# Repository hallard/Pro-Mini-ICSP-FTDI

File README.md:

Arduino Pro Mini ICSP and FTDI Programming Board
================================================

This shield is used to flash my Arduino Pro Mini with [OptiBoot](https://github.com/Optiboot/optiboot) bootloader and to upload sketch to it. Optiboot is less Flash consuming than classic one.

Also, for 3V3 at 8MHz devices, upload at 57600 is slow, so I'm using 250KBPS upload. You can see [here](https://hallard.me/ulpnode-bootloader-1/) why and how to. 
So, I can upload faster and more than that, Optiboot is using 0.5K of flash instead of 2K, it's a double win configuration, especially with huge sketch like LoraWan device with LMIC stack for my [Mini LORA Board](https://www.thethingsnetwork.org/forum/t/8059/).

**Features**   

- ICSP 6 pins connector
- FTDI 6 pins connector
- Power LED
- Reset button

**Got V1.0 Boards from [PCBs.io](https://PCBs.io). I tested them, all is fine**

Detailed Description
====================

Nothing special to say, it's just some wiring, ICSP pins for programming (Power+SPI+Reset), FTDI (Power+Reset+RX+TX) for flashing and a LED to power the board (see if ICSP connector is fitted with good pining)

I'm using 2 PCB boards stacked with pogo pins and this avoid soldering any headers to the Mini Boards. 

Schematics
==========

Click on image to zoom   

Boards
====== 

**Top**

**Bottom**

You can order PCB at [PCBs.io](https://PCBs.io/share/rm2v2). PCBs.io give me reward when you order my designed boards from their site. This is pretty good, because I can use these rewards to create and design new boards and order boards for a discounted price and share new boards. So if you don't care about PCB manufacturer please use PCBs.io.

Assembled boards (V1.0)
=======================

**Populated**

**With Arduino Pro Mini on it**

Bootloaders
===========

I've compiled some [bootloaders](https://github.com/hallard/Pro-Mini-ICSP-FTDI/tree/master/bootloaders) for you, use the one you prefer, I'm using:

- optiboot_flash_atmega328p_250000_8MHZ.hex (250KBPS) on 3V3 8MHz Mini
- optiboot_flash_atmega328p_250000_16MHZ.hex on 5V 16MHz Mini

I tested the 1MB ones, works fine also, here below the configuration of Fuses and Lockbit I'm using.

**Fuse configuration**

**Lockbit**

License
=======

This work is licensed under a Creative Commons Attribution-NonCommercial 4.0 International [License](http://creativecommons.org/licenses/by-nc/4.0)

If you want to do commercial stuff with this project, please contact [CH2i company](https://ch2i.eu) so we can organize an simple agreement.

Misc
====
See news and other projects on my [blog](https://hallard.me)

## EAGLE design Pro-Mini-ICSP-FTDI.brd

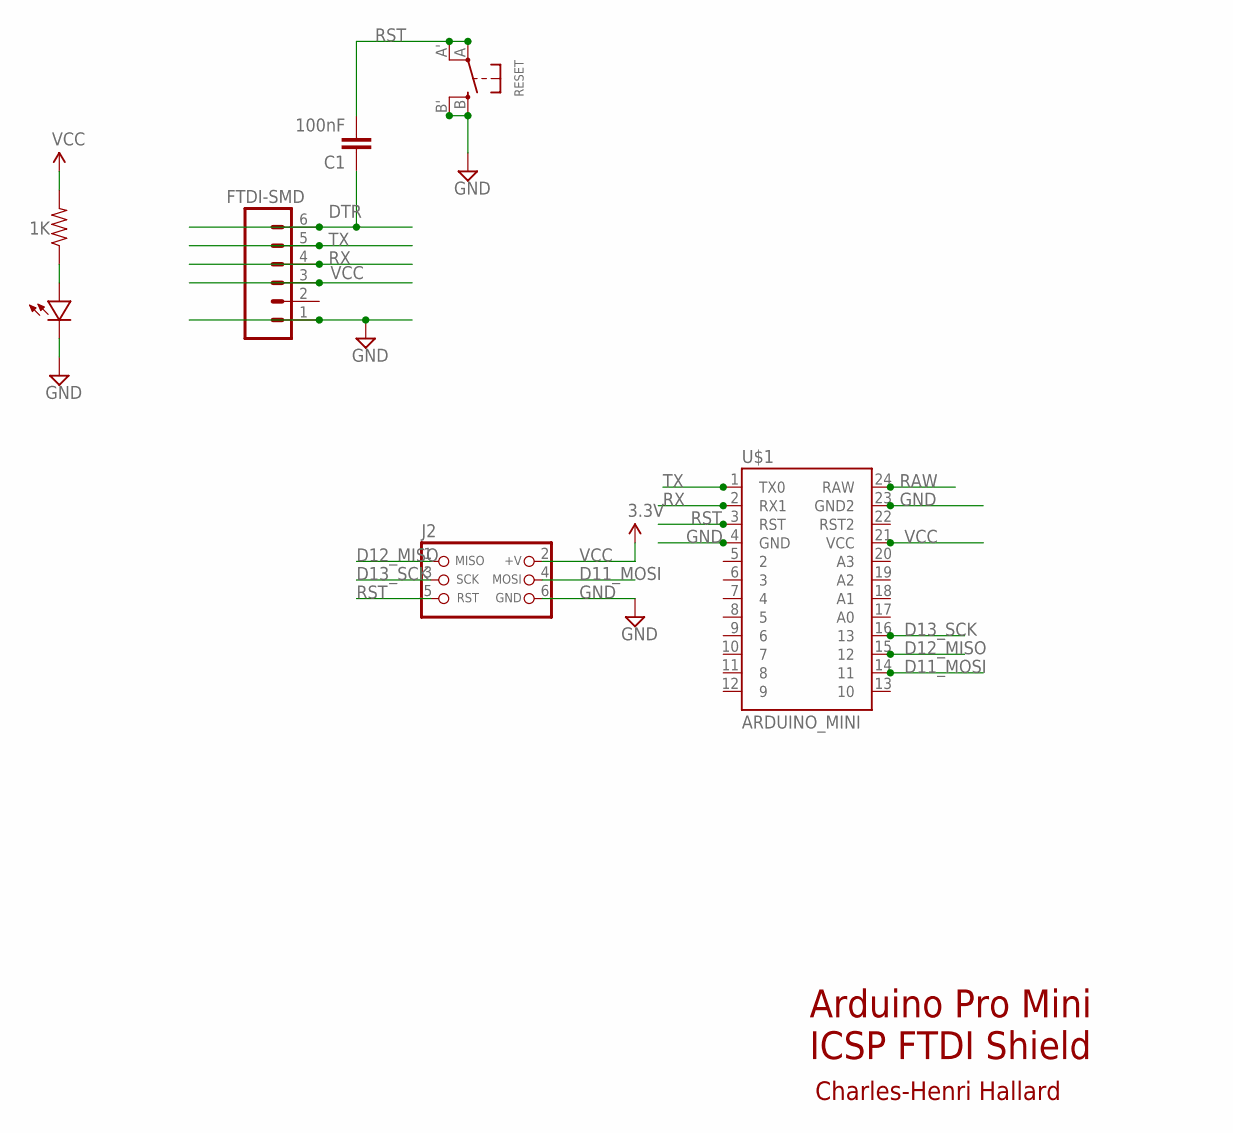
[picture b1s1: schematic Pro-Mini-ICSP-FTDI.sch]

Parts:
C1: 100nF; 0805-CAP
FTDI-SMD: SMD; 1X06
J2: CON_HEADER_PRG_AVR_ICSP-PTH; HEADER_PRG_2X03
R1: 1K; 0805-RES
RESET: SWITCH_TACT_SMT; EVQ-Q2
U$1: ARDUINO_MINI
U$2: LED0805; 0805-LED

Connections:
D11_MOSI: J2.4 (MOSI), U$1.14 (11)
D12_MISO: J2.1 (MISO), U$1.15 (12)
D13_SCK: J2.3 (SCK), U$1.16 (13)
DTR: C1.1, FTDI-SMD.6
GND: FTDI-SMD.1, J2.6 (GND), RESET.B (S), RESET.B' (S1), U$1.4 (GND), U$1.23 (GND2), U$2.MINUS
unnamed: R1.1, U$2.PLUS
RAW: U$1.24 (RAW)
RST: C1.2, J2.5 (RST), RESET.A, RESET.A' (P1), U$1.3 (RST)
RX: FTDI-SMD.4, U$1.2 (RX1)
TX: FTDI-SMD.5, U$1.1 (TX0)
VCC: FTDI-SMD.3, J2.2 (+V), R1.2, U$1.21 (VCC)

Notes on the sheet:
Arduino Pro Mini ICSP FTDI Shield
Charles-Henri Hallard

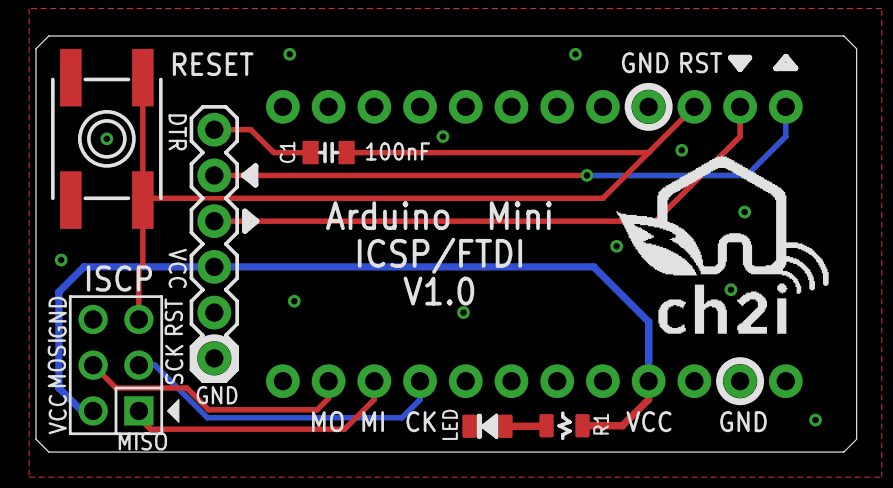
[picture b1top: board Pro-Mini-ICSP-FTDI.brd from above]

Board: 2 copper layers, 45.6 x 23.1 mm, 9 parts (1 on the bottom side), 10 nets.

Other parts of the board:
U$3, U$4: LOGO_CH2I_110MM

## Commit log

2017-07-24 :lollipop: Added .gitattributes
2017-07-24 Creation
2017-07-24 Links
2017-07-24 Link error
2017-07-25 Changed with real pictures
2017-07-25 Added pictures
2017-07-25 Removed top
2017-07-25 Added fuses and lockbit
2017-07-25 cosmetic
2017-07-25 Cropped

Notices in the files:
parts and their libraries:
SparkFun-Connectors: Licensing: CC v3.0 Share-Alike You are welcome to use this library for commercial purposes.
microbuilder: This work is placed in the public domain, and may be freely used for commercial and non-commercial work with the following conditions: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
